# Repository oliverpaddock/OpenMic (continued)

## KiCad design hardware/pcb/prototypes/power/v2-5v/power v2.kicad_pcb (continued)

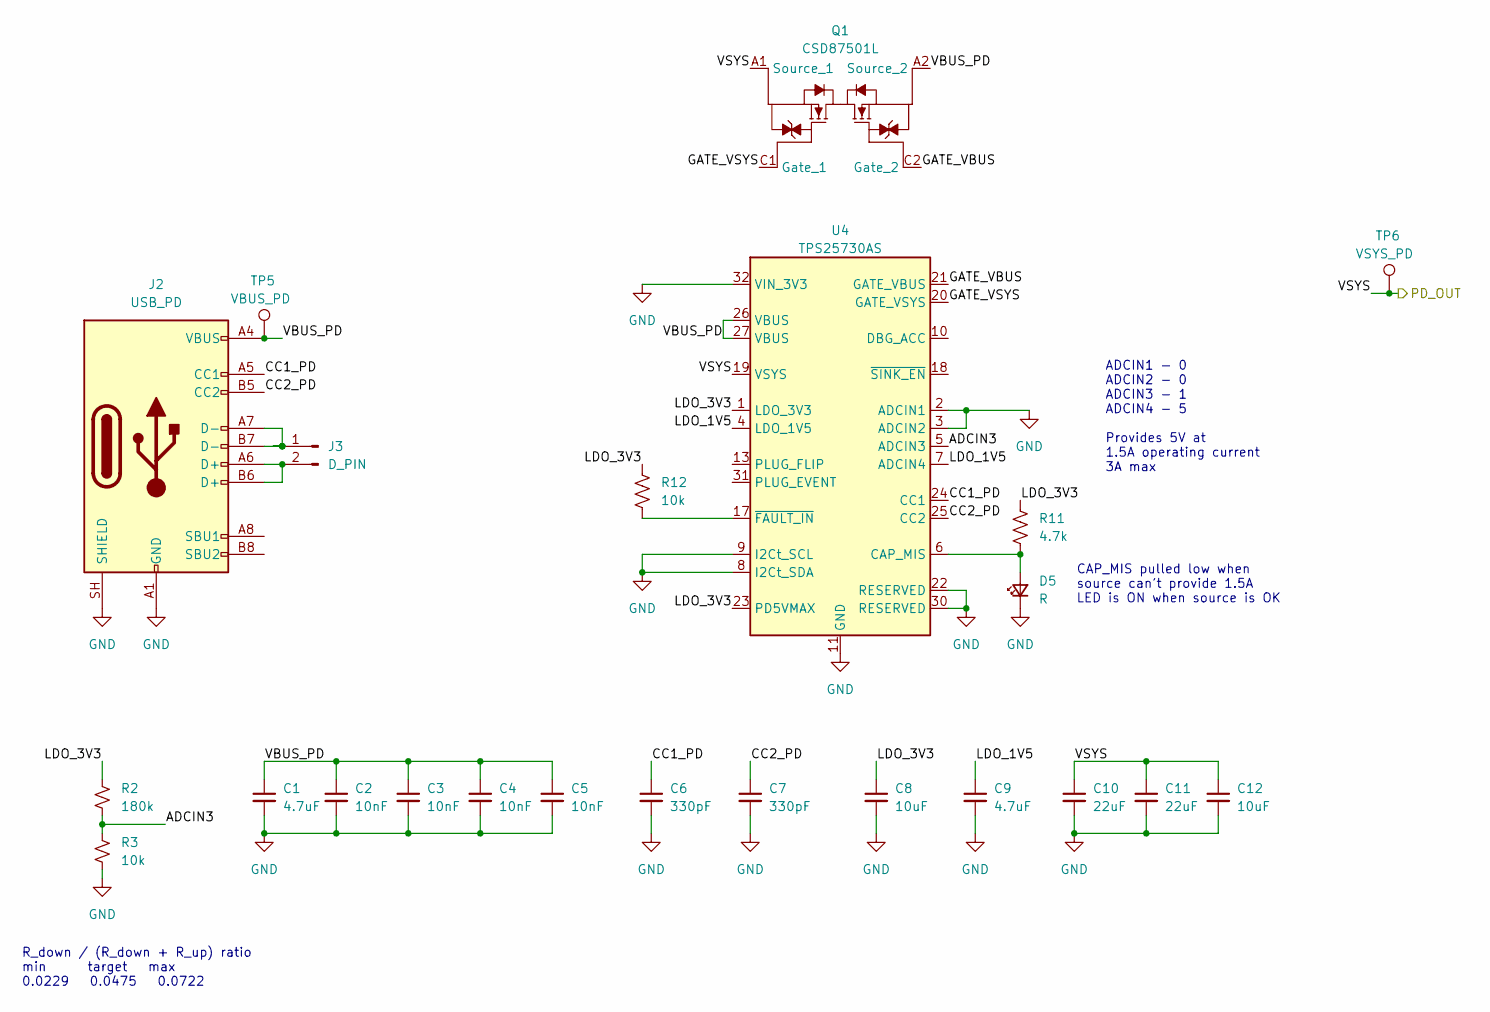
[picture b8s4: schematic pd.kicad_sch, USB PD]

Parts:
C1: 4.7uF; C_0805_2012Metric_Pad1.18x1.45mm_HandSolder; Rating 25V
C2, C3, C4, C5: 10nF; C_0805_2012Metric_Pad1.18x1.45mm_HandSolder; Rating 25V
C6, C7: 330pF; C_0805_2012Metric_Pad1.18x1.45mm_HandSolder; Rating 6.3V
C8: 10uF; C_0805_2012Metric_Pad1.18x1.45mm_HandSolder; Rating 6.3V
C9: 4.7uF; C_0805_2012Metric_Pad1.18x1.45mm_HandSolder; Rating 4V
C10, C11: 22uF; C_0805_2012Metric_Pad1.18x1.45mm_HandSolder; Rating 25V
C12: 10uF; C_0805_2012Metric_Pad1.18x1.45mm_HandSolder; Rating 25V
D5: R; LED_0805_2012Metric_Pad1.15x1.40mm_HandSolder
J2: USB_PD; USB_C_Receptacle_HRO_TYPE-C-31-M-12
J3: D_PIN; PinHeader_1x02_P1.00mm_Vertical
Q1: CSD87501L; BGA-10_P0.65mm; MPN CSD87501L
R2: 180k; R_0805_2012Metric_Pad1.20x1.40mm_HandSolder
R3, R12: 10k; R_0805_2012Metric_Pad1.20x1.40mm_HandSolder
R11: 4.7k; R_0805_2012Metric_Pad1.20x1.40mm_HandSolder
TP5: VBUS_PD; TestPoint_Pad_1.5x1.5mm
TP6: VSYS_PD; TestPoint_Pad_1.5x1.5mm
U4: TPS25730AS; VQFN-32-1EP_4x4mm_P0.4mm_EP2.8x2.8mm; MPN TPS25730ASRSMR

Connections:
/5V PD/ADCIN3: R2.2, R3.1, U4.5 (ADCIN3)
/5V PD/CC1_PD: C6.1, J2.A5 (CC1), U4.24 (CC1)
/5V PD/CC2_PD: C7.1, J2.B5 (CC2), U4.25 (CC2)
/5V PD/GATE_VBUS: Q1.C2 (Gate_2), U4.21 (GATE_VBUS)
/5V PD/GATE_VSYS: Q1.C1 (Gate_1), U4.20 (GATE_VSYS)
/5V PD/LDO_1V5: C9.1, U4.4 (LDO_1V5), U4.7 (ADCIN4)
/5V PD/LDO_3V3: C8.1, R2.1, R11.2, R12.2, U4.1 (LDO_3V3), U4.23 (PD5VMAX)
/5V PD/VBUS_PD: C1.1, C2.1, C3.1, C4.1, C5.1, J2.A4 (VBUS), J2.A9 (VBUS), J2.B4 (VBUS), J2.B9 (VBUS), Q1.A2 (Source_2), Q1.B2 (Source_1), Q1.D2 (Source_1), Q1.E2 (Source_1), TP5.1 (1_1), U4.26 (VBUS), U4.27 (VBUS)
/5V PD/VSYS: C10.1, C11.1, C12.1, Q1.A1 (Source_1), Q1.B1 (Source_1), Q1.D1 (Source_1), Q1.E1 (Source_1), TP6.1 (1_1), U4.19 (VSYS); also elsewhere on the board
GND: C1.2, C2.2, C3.2, C4.2, C5.2, C6.2, C7.2, C8.2, C9.2, C10.2, C11.2, C12.2, D5.1 (K), J2.A1 (GND), J2.A12 (GND), J2.B1 (GND), J2.B12 (GND), J2.SH (SHIELD), R3.2, U4.2 (ADCIN1), U4.3 (ADCIN2), U4.8 (I2Ct_SDA), U4.9 (I2Ct_SCL), U4.11 (GND), U4.12 (GND), U4.14 (GND), U4.15 (GND), U4.16 (GND), U4.22 (RESERVED), U4.28 (GND), U4.29 (GND), U4.30 (RESERVED), U4.32 (VIN_3V3), U4.33 (GND); also elsewhere on the board
unnamed: D5.2 (A), R11.1, U4.6 (CAP_MIS)
unnamed: J2.A7 (D-), J2.B7 (D-), J3.1
unnamed: J2.A6 (D+), J2.B6 (D+), J3.2
unnamed: R12.1, U4.17 (~FAULT_IN)

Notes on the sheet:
CAP_MIS pulled low when source can't provide 1.5A LED is ON when source is OK
R_down / (R_down + R_up) ratio min target max 0.0229 0.0475 0.0722
ADCIN1 - 0 ADCIN2 - 0 ADCIN3 - 1 ADCIN4 - 5 Provides 5V at 1.5A operating current 3A max

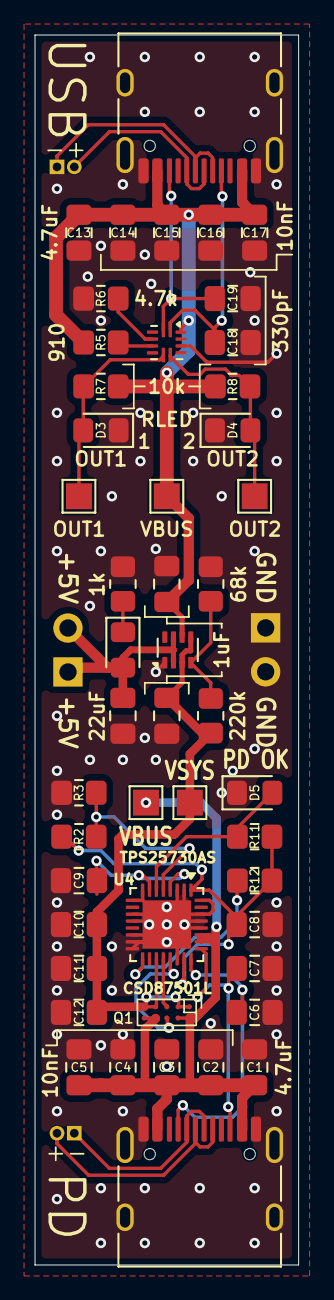
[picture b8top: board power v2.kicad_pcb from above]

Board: 2 copper layers, 15.2 x 71.1 mm, 52 parts (0 on the bottom side), 26 nets.

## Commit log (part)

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2023-05-16 Create info.txt
    create kicad folder
2023-05-16 add kicad files
2023-06-09 Add src and CAD
2025-04-08 Update LICENSE to CERN-OHL-S
2025-04-09 added kicad and schematics
2025-04-09 added datasheets
2025-04-09 added input simulation
2026-03-18 project organization
2026-03-18 next steps
2026-03-19 improved circuit
2026-03-19 added references
2026-03-20 clip circuit improvements
2026-03-20 crossfader improvements
2026-03-20 removed extra mon
2026-03-20 crossfader updates
2026-03-21 changed to 9v rails and OPA1612
2026-03-21 fixed ground symbols and spacing
2026-03-21 changed to 9v rails
2026-03-21 gain and rails (#4)
2026-03-21 15v rails
2026-03-21 1k led resistors
2026-03-21 15v rails and 5532 amp
2026-03-23 5532's and TL072's everywhere
2026-03-23 phantom power
2026-03-23 gain stage
2026-03-23 added project structure
2026-03-24 added structure and dual input
2026-03-24 direct monitor switch (#5)
2026-03-25 phantom switch (#6)
2026-03-25 net labels
2026-03-27 line output gain staging
2026-03-27 line out connections
2026-03-27 headphone driver (#7)
2026-03-31 mic input (#10)
2026-04-01 added TXE8124 and THAT5263
2026-04-02 added xu316
2026-04-03 XU316 as usb device
2026-04-03 +/-15V power supply
2026-04-03 added PS ref
2026-04-03 power supplies
2026-04-03 moved phantom power to power supply
2026-04-06 rotary encoder
2026-04-06 WS2812 input array
2026-04-06 remove clip circuit
2026-04-08 closing #8
2026-04-08 tac5212 initial architecture
2026-04-08 phones out
2026-04-08 line out
2026-04-08 input enable
2026-04-10 monitor switch
2026-04-14 external power supply (#9)
2026-04-14 CH224K external supply
2026-04-15 bypass caps
2026-04-15 replace 2N7002 with CSD13380F3
2026-04-15 add spice models
2026-04-17 usb power supply sim
2026-04-20 simulation power supplies
2026-04-20 add gitignore
2026-04-20 remove ignored files from repo
2026-04-20 xlr input sim
2026-04-22 inst/line inverter
2026-04-22 line simulation
2026-04-22 inst simulation
2026-04-22 OPA1637 impedance/inverter phase correction
2026-04-22 layout updates
2026-04-22 ac coupled inputs
2026-04-22 remove mic vbias from inputs
2026-04-22 output stage impedances
2026-04-22 output sim
2026-04-23 added protection diodes
2026-04-24 power supply footprints
2026-04-24 push buttons
2026-04-26 revert input.asc to last commit
2026-04-26 reduced ws2812 count
2026-05-04 added footprints
2026-05-05 footprint selection
2026-05-06 footprints
2026-05-07 xlr ind (#16)
2026-05-07 update ch224k vdd
2026-05-07 +/-15V supply output
2026-05-07 started power test board
2026-05-08 added test points
2026-05-08 board footprint layout
2026-05-09 power board first draft
2026-05-11 trace widths
2026-05-12 bom update
2026-05-13 standard jlc resistor values
2026-05-13 fabrication outputs
2026-05-13 add JLC and MPN to BOM
2026-05-14 INA1650 (#10)
2026-05-14 power board layout updates
2026-05-15 output schematic pdfs
2026-05-18 moved power test board folder
2026-05-20 input test schematic
2026-05-20 update schematics
2026-05-21 TVS phantom protection diodes
2026-05-21 add footprints
2026-05-21 added mcu test schematic
2026-05-21 sch updates
2026-05-24 footprint assignments
2026-05-26 pcb layout
2026-06-01 add aisler sponsorship
2026-06-01 add blog link
2026-06-05 add sponsor
2026-06-06 spacing
